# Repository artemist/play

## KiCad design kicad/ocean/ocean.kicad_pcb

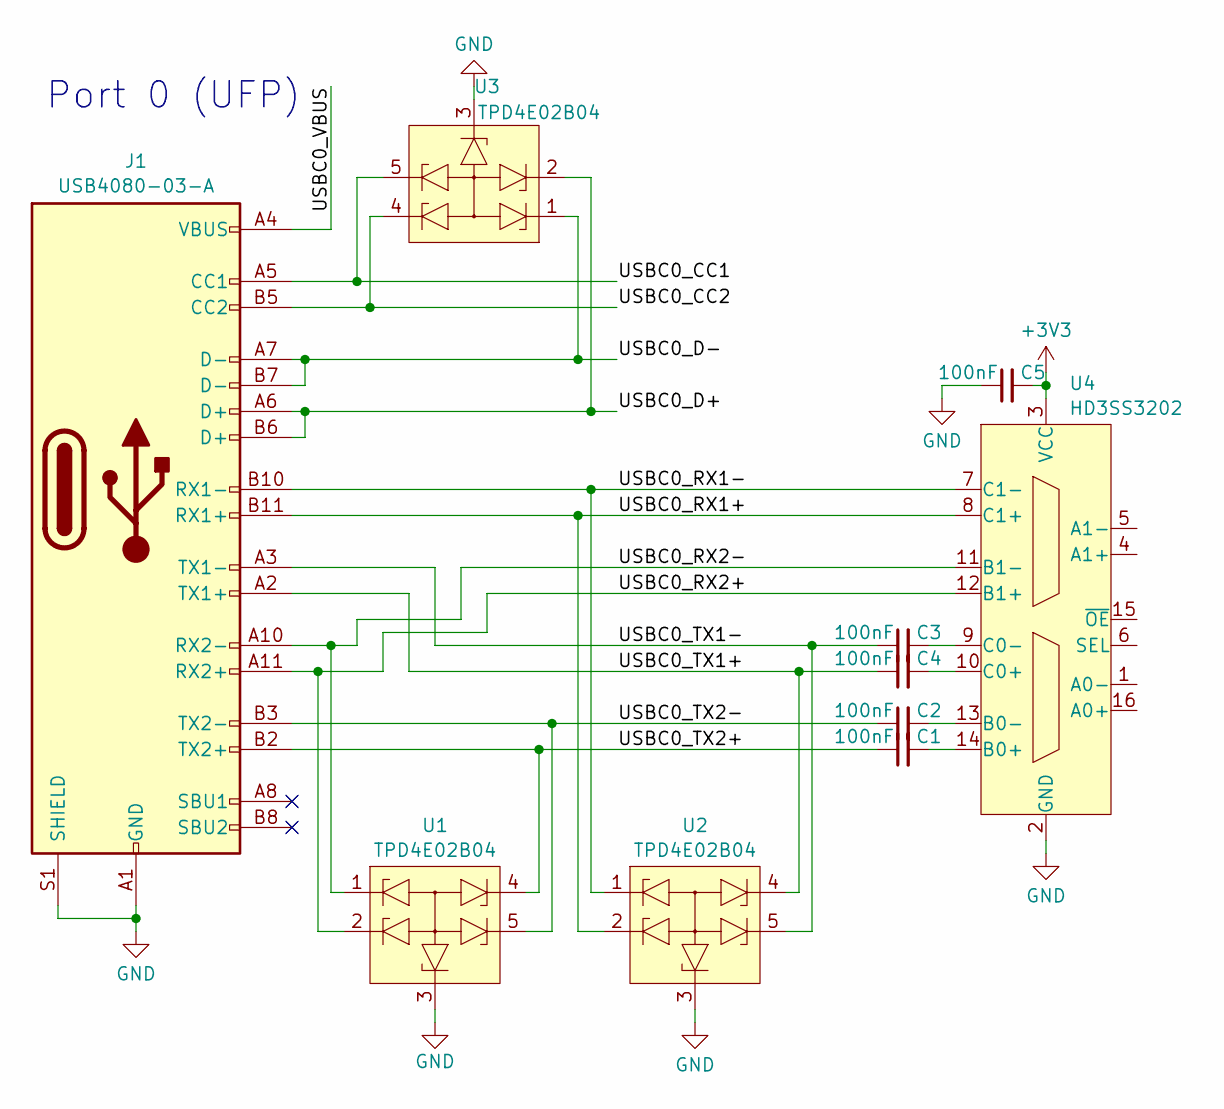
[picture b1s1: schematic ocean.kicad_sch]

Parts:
C1, C2, C3, C4, C5: 100nF; C_0402_1005Metric
J1: USB4080-03-A; USB_C_Receptacle_GCT_USB4080
U1, U2, U3: TPD4E02B04; USON-10_2.5x1.0mm_P0.5mm
U4: HD3SS3202; Texas_UQFN-16_1.8x2.6mm_P0.4mm

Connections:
+3V3: C5.2, U4.3 (VCC)
/USBC0_CC1: J1.A5 (CC1), U3.5 (CH4), U3.6 (NC)
/USBC0_CC2: J1.B5 (CC2), U3.4 (CH3), U3.7 (NC)
/USBC0_D+: J1.A6 (D+), J1.B6 (D+), U3.2 (CH2), U3.9 (NC)
/USBC0_D-: J1.A7 (D-), J1.B7 (D-), U3.1 (CH1), U3.10 (NC)
/USBC0_RX1+: J1.B11 (RX1+), U2.2 (CH2), U2.9 (NC), U4.8 (C1+)
/USBC0_RX1-: J1.B10 (RX1-), U2.1 (CH1), U2.10 (NC), U4.7 (C1-)
/USBC0_RX2+: J1.A11 (RX2+), U1.2 (CH2), U1.9 (NC), U4.12 (B1+)
/USBC0_RX2-: J1.A10 (RX2-), U1.1 (CH1), U1.10 (NC), U4.11 (B1-)
/USBC0_TX1+: C4.1, J1.A2 (TX1+), U2.4 (CH3), U2.7 (NC)
/USBC0_TX1-: C3.1, J1.A3 (TX1-), U2.5 (CH4), U2.6 (NC)
/USBC0_TX2+: C1.1, J1.B2 (TX2+), U1.4 (CH3), U1.7 (NC)
/USBC0_TX2-: C2.1, J1.B3 (TX2-), U1.5 (CH4), U1.6 (NC)
/USBC0_VBUS: J1.A4 (VBUS), J1.A9 (VBUS), J1.B4 (VBUS), J1.B9 (VBUS)
GND: C5.1, J1.A1 (GND), J1.A12 (GND), J1.B1 (GND), J1.B12 (GND), J1.S1 (SHIELD), U1.3 (GND), U1.8 (GND), U2.3 (GND), U2.8 (GND), U3.3 (GND), U3.8 (GND), U4.2 (GND)
unnamed: C1.2, U4.14 (B0+)
unnamed: C2.2, U4.13 (B0-)
unnamed: C4.2, U4.10 (C0+)
unnamed: C3.2, U4.9 (C0-)

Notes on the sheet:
Port 0 (UFP)

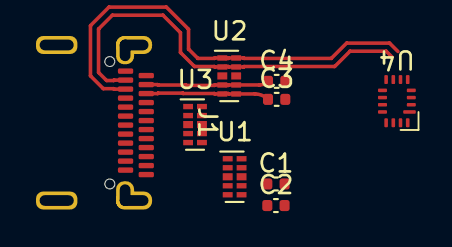
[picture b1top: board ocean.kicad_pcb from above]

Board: 4 copper layers, 10 parts (1 on the bottom side), 19 nets.

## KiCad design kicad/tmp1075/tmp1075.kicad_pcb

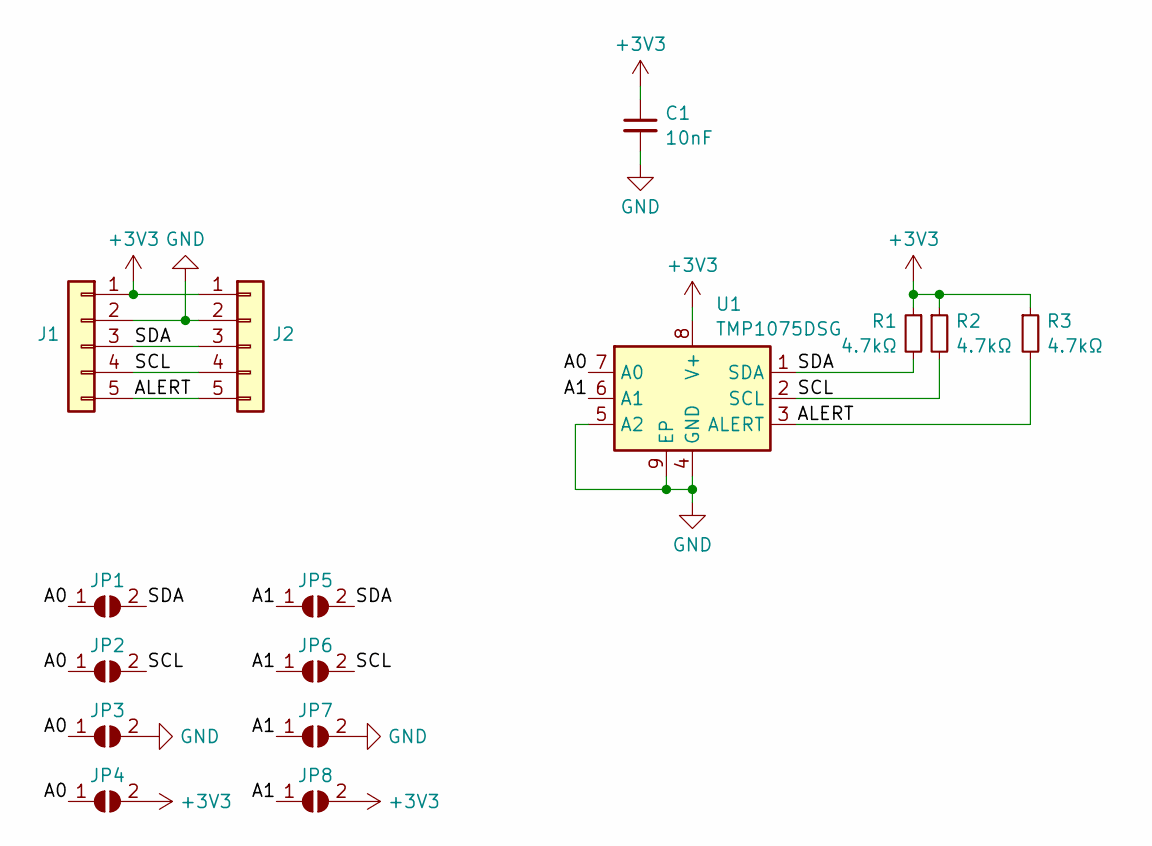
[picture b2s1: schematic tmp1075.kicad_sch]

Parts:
C1: 10nF; C_0402_1005Metric
J1, J2: Conn_01x05; PinHeader_1x05_P1.00mm_Vertical
JP1, JP2, JP3, JP4, JP5, JP6, JP7, JP8: SolderJumper_2_Open; R_0201_0603Metric
R1, R2, R3: 4.7kΩ; R_0402_1005Metric
U1: TMP1075DSG; WSON-8-1EP_2x2mm_P0.5mm_EP0.9x1.6mm_ThermalVias

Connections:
+3V3: C1.1, J1.1, J2.1, JP4.2 (B), JP8.2 (B), R1.1, R2.1, R3.1, U1.8 (V+)
/A0: JP1.1 (A), JP2.1 (A), JP3.1 (A), JP4.1 (A), U1.7 (A0)
/A1: JP5.1 (A), JP6.1 (A), JP7.1 (A), JP8.1 (A), U1.6 (A1)
/ALERT: J1.5, J2.5, R3.2, U1.3 (ALERT)
/SCL: J1.4, J2.4, JP2.2 (B), JP6.2 (B), R2.2, U1.2 (SCL)
/SDA: J1.3, J2.3, JP1.2 (B), JP5.2 (B), R1.2, U1.1 (SDA)
GND: C1.2, J1.2, J2.2, JP3.2 (B), JP7.2 (B), U1.4 (GND), U1.5 (A2), U1.9 (EP)

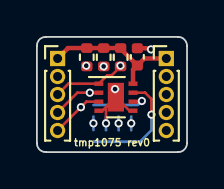
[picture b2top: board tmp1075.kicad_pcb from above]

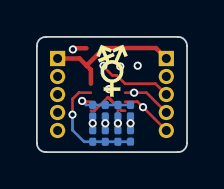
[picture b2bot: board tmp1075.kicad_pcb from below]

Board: 4 copper layers, 8.3 x 6.4 mm, 15 parts (8 on the bottom side), 7 nets.

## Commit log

2018-08-23 add wordpw
2018-08-23 Minor wordpw changes
2018-09-14 Start pppassword
2018-12-09 A bunch of changers I neglected to commit earlier
    Strange size things (i7 in llvm)
    Hellp world in idris
    A rolldice test
    pppassword changes to add b
2018-12-10 Play more with strange bit sizes
2018-12-10 i65 is super weird
2019-04-25 Add wii rename and strange_size script
2019-04-25 Switch executable scripts to use nix-shell
2020-01-29 add scripts, the start of a monte-carlo
2022-01-17 Start playing with device trees
2022-05-30 Add some embedded stuff
2022-06-02 Add SCD30 test
2022-10-04 Update pico SDK
2022-10-05 ... it's sht30 not scd30
2023-08-12 Apparently I was doing stuff
2023-08-13 Add tmp1075 breakout that jlc doesn't like
2023-08-29 take 2 on tmp1075 breakout
2023-08-31 Try making a stamp holder
2023-08-31 alignment hole should be better now
2023-10-07 Stamp holder changes
2023-10-07 Add some projects from the hackerspace
2023-10-07 Change the owen focus ring to work with non-flexible filament
2023-11-12 Add flake for zephyr dev
2023-11-12 zephyr/blink: copy in example to show how to build
2023-11-13 Try adding w5500-test, though it doesn't fit
2023-11-16 w5500-test on rpi pico, but it doesn't work
2024-02-04 old zephyr sam3s port template
2024-02-04 move files
2024-02-04 add cat_esd.svg
2024-02-09 start ideas for usb hub
2024-02-09 add tc2030 to swd adapter, hopefully it's right
2024-02-23 fix zephyr dev shell
2024-03-15 add hacky yuzu2ryujinx script
2024-03-16 yuzu2ryujinx: correct comment
2024-03-22 add label
2024-03-24 let's try rust embedded again
2024-03-24 okay rust-embedded tooling has improved a lot
2024-03-24 Well I guess I can build for lpc1114
2024-03-25 blink on lpc1114
2024-03-25 cargo embed doesn't like lpc1114 or tigard, just use openocd
2024-03-25 okay let's try to make our own pac (it doesn't work)
2024-03-25 i made my own pac for some reason
2024-03-25 add get_discord_emoji script because that's fun
